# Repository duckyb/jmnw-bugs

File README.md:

# Bugs

Opinionated ergonomic keyboards.

## Flea v0.1

| Front | Back |
| :---: | :---: |
|  |  |

## Gnat v0.2.1

| Front | Back |
| :---: | :---: |
|  |  |

## Midge v0.3

| Front | Back |
| :---: | :---: |
|  |  |

## Mosquito v0.1.1

| Front | Back |
| :---: | :---: |
|  |  |

## Wasp v0.1.1

| Front | Back |
| :---: | :---: |
|  |  |

## Yellowjacket v0.1.2

| Front | Back |
| :---: | :---: |
|  |  |

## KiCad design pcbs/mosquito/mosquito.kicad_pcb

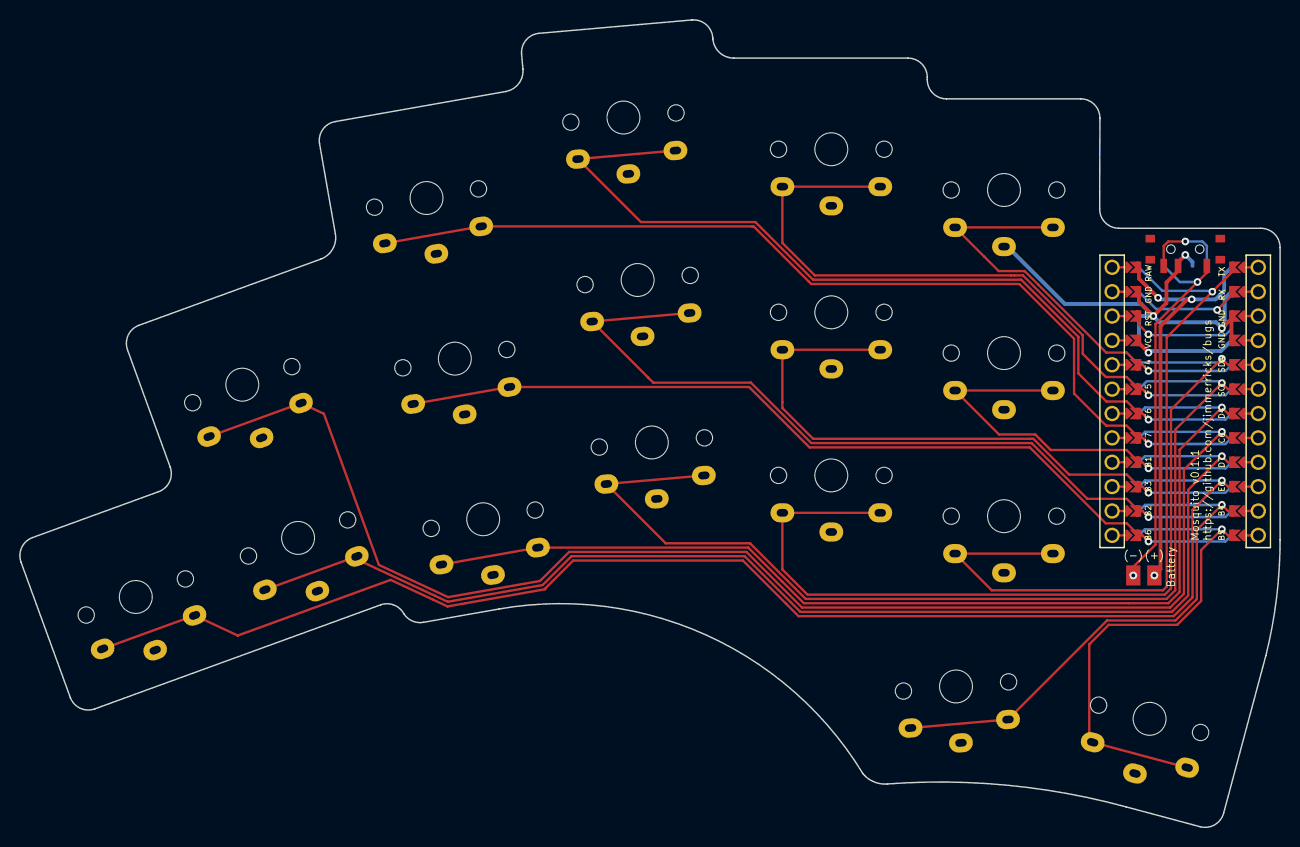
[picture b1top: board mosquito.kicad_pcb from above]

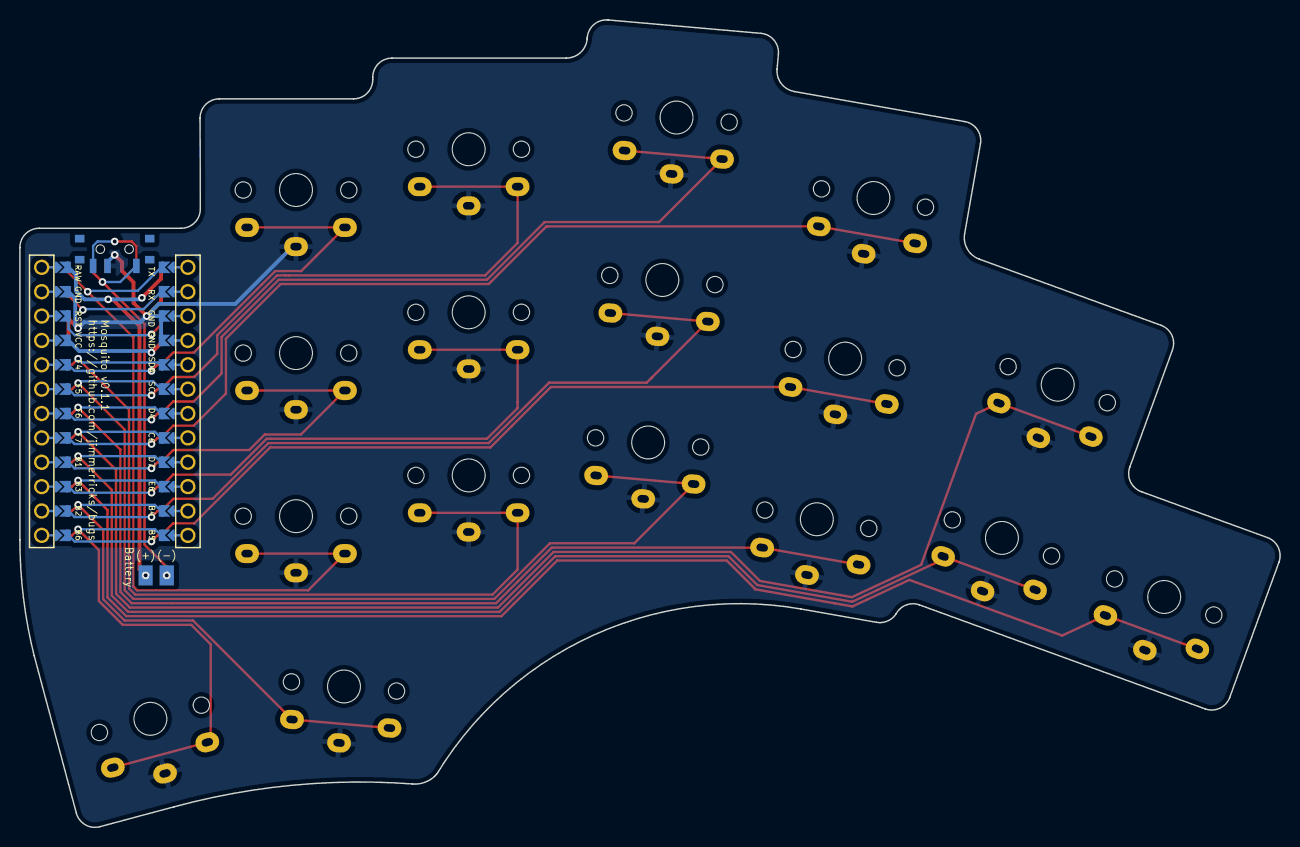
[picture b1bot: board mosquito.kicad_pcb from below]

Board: 2 copper layers, 131.4 x 84.2 mm, 23 parts (3 on the bottom side), 20 nets.

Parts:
BT1: Battery_Cell; Battery_pads_reversible
PSW1: SW_SPDT; Power_reversible
Ref**: Val**; thread_m2
Ref**#2, Ref**#3: Val**; thread_m2
SW1, SW2, SW3, SW4, SW5, SW6, SW7, SW8, SW9, SW10, SW11, SW12, SW13, SW14, SW15, SW16, SW17: SW_PUSH; Choc_reversible
U1: ProMicro; ProMicro_jumpers

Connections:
GND: PSW1.2 (B), SW1.2, SW2.2, SW3.2, SW4.2, SW5.2, SW6.2, SW7.2, SW8.2, SW9.2, SW10.2, SW11.2, SW12.2, SW13.2, SW14.2, SW15.2, SW16.2, SW17.2, U1.3 (GND), U1.4 (GND), U1.23 (GND)
unnamed: BT1.2 (-), PSW1.1 (A)
raw: BT1.1 (+), U1.24 (RAW)
switch1: SW1.1, U1.8 (C6)
switch2: SW2.1, U1.17 (F7)
switch3: SW3.1, U1.18 (F6)
switch4: SW4.1, U1.19 (F5)
switch5: SW5.1, U1.20 (F4)
switch6: SW6.1, U1.9 (D7)
switch7: SW7.1, U1.13 (B6)
switch8: SW8.1, U1.14 (B2)
switch9: SW9.1, U1.15 (B3)
switch10: SW10.1, U1.16 (B1)
switch11: SW11.1, U1.10 (E6)
switch12: SW12.1, U1.7 (D4)
switch13: SW13.1, U1.6 (SCL)
switch14: SW14.1, U1.5 (SDA)
switch15: SW15.1, U1.1 (TX)
switch16: SW16.1, U1.11 (B4)
switch17: SW17.1, U1.12 (B5)

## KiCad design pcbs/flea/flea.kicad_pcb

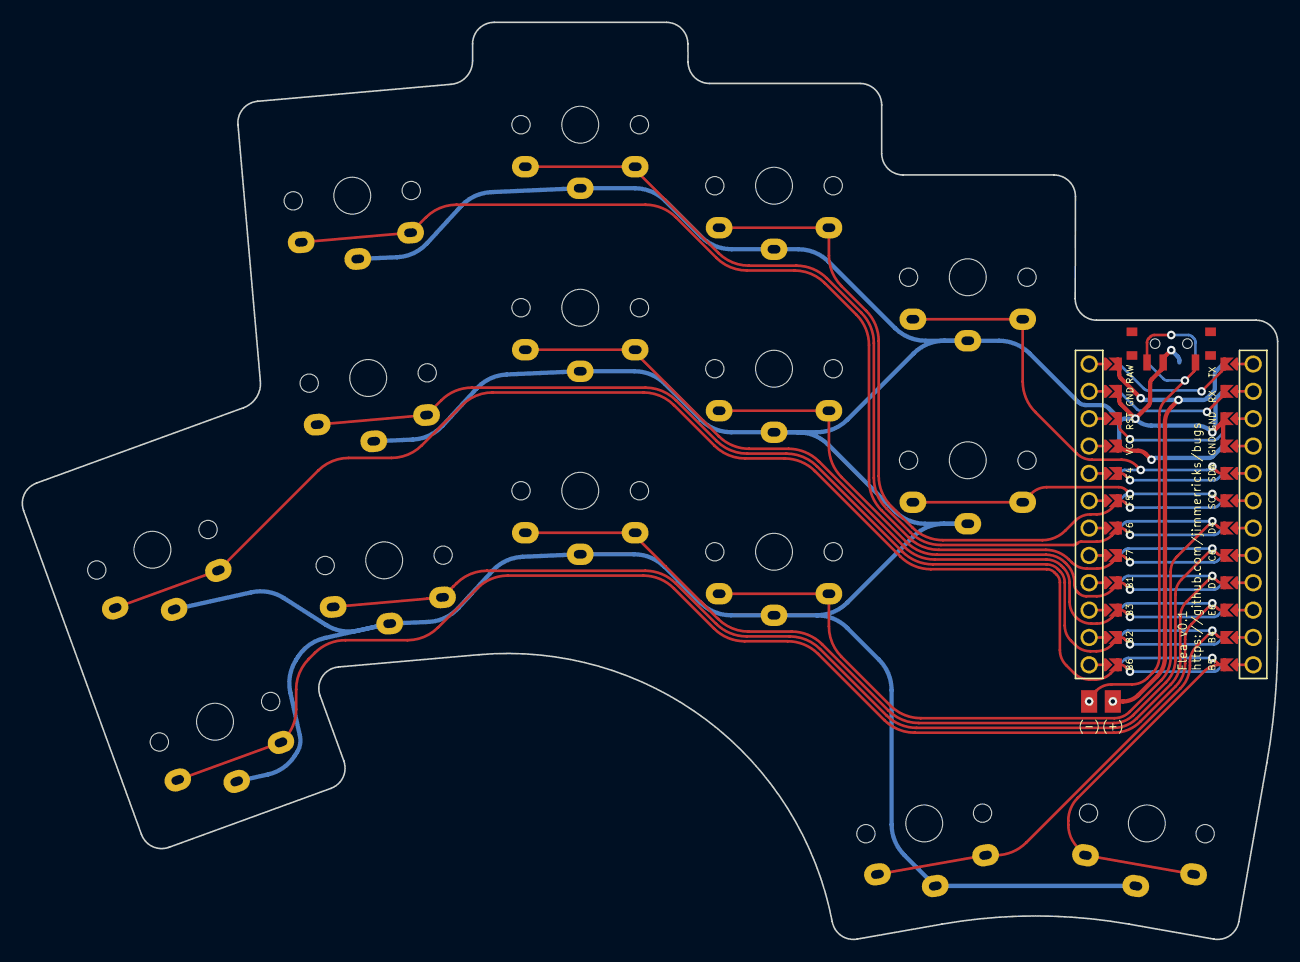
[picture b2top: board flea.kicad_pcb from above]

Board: 2 copper layers, 116.6 x 85.2 mm, 19 parts (1 on the bottom side), 18 nets.

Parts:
BT1: Battery_Cell; Battery_pads_reversible
PSW1: SW_SPDT; Power_reversible
Ref**: Val**; thread_m2
SW1, SW2, SW3, SW4, SW5, SW6, SW7, SW8, SW9, SW10, SW11, SW12, SW13, SW14, SW15: SW_PUSH; Choc_reversible
U1: ProMicro; ProMicro_jumpers

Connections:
GND: PSW1.2 (B), SW1.2, SW2.2, SW3.2, SW4.2, SW5.2, SW6.2, SW7.2, SW8.2, SW9.2, SW10.2, SW11.2, SW12.2, SW13.2, SW14.2, SW15.2, U1.3 (GND), U1.4 (GND), U1.23 (GND)
unnamed: BT1.2 (-), PSW1.1 (A)
raw: BT1.1 (+), U1.24 (RAW)
switch1: SW1.1, U1.17 (F7)
switch2: SW2.1, U1.18 (F6)
switch3: SW3.1, U1.19 (F5)
switch4: SW4.1, U1.5 (SDA)
switch5: SW5.1, U1.13 (B6)
switch6: SW6.1, U1.14 (B2)
switch7: SW7.1, U1.15 (B3)
switch8: SW8.1, U1.16 (B1)
switch9: SW9.1, U1.6 (SCL)
switch10: SW10.1, U1.10 (E6)
switch11: SW11.1, U1.9 (D7)
switch12: SW12.1, U1.8 (C6)
switch13: SW13.1, U1.7 (D4)
switch14: SW14.1, U1.11 (B4)
switch15: SW15.1, U1.12 (B5)

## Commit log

2022-08-09 Add automated workflows for images
2022-08-09 Update workflow file
2022-08-09 Update gallery (automated)
2022-08-09 Update workflow using matrix
2022-08-09 Add ant folder
2022-08-09 Add bug folders
2022-08-09 Use single job
2022-08-09 Remove checkout during second step
2022-08-09 Add build environment
2022-08-09 Fix build environment
2022-08-09 Update checkout action
2022-08-09 Do not clean repository before checking out
2022-08-09 Try removing ref
2022-08-10 Update workflow
2022-08-10 Update flea edge
2022-08-10 Upgrade kikit
2022-08-10 Update gnat & mosquito edge
